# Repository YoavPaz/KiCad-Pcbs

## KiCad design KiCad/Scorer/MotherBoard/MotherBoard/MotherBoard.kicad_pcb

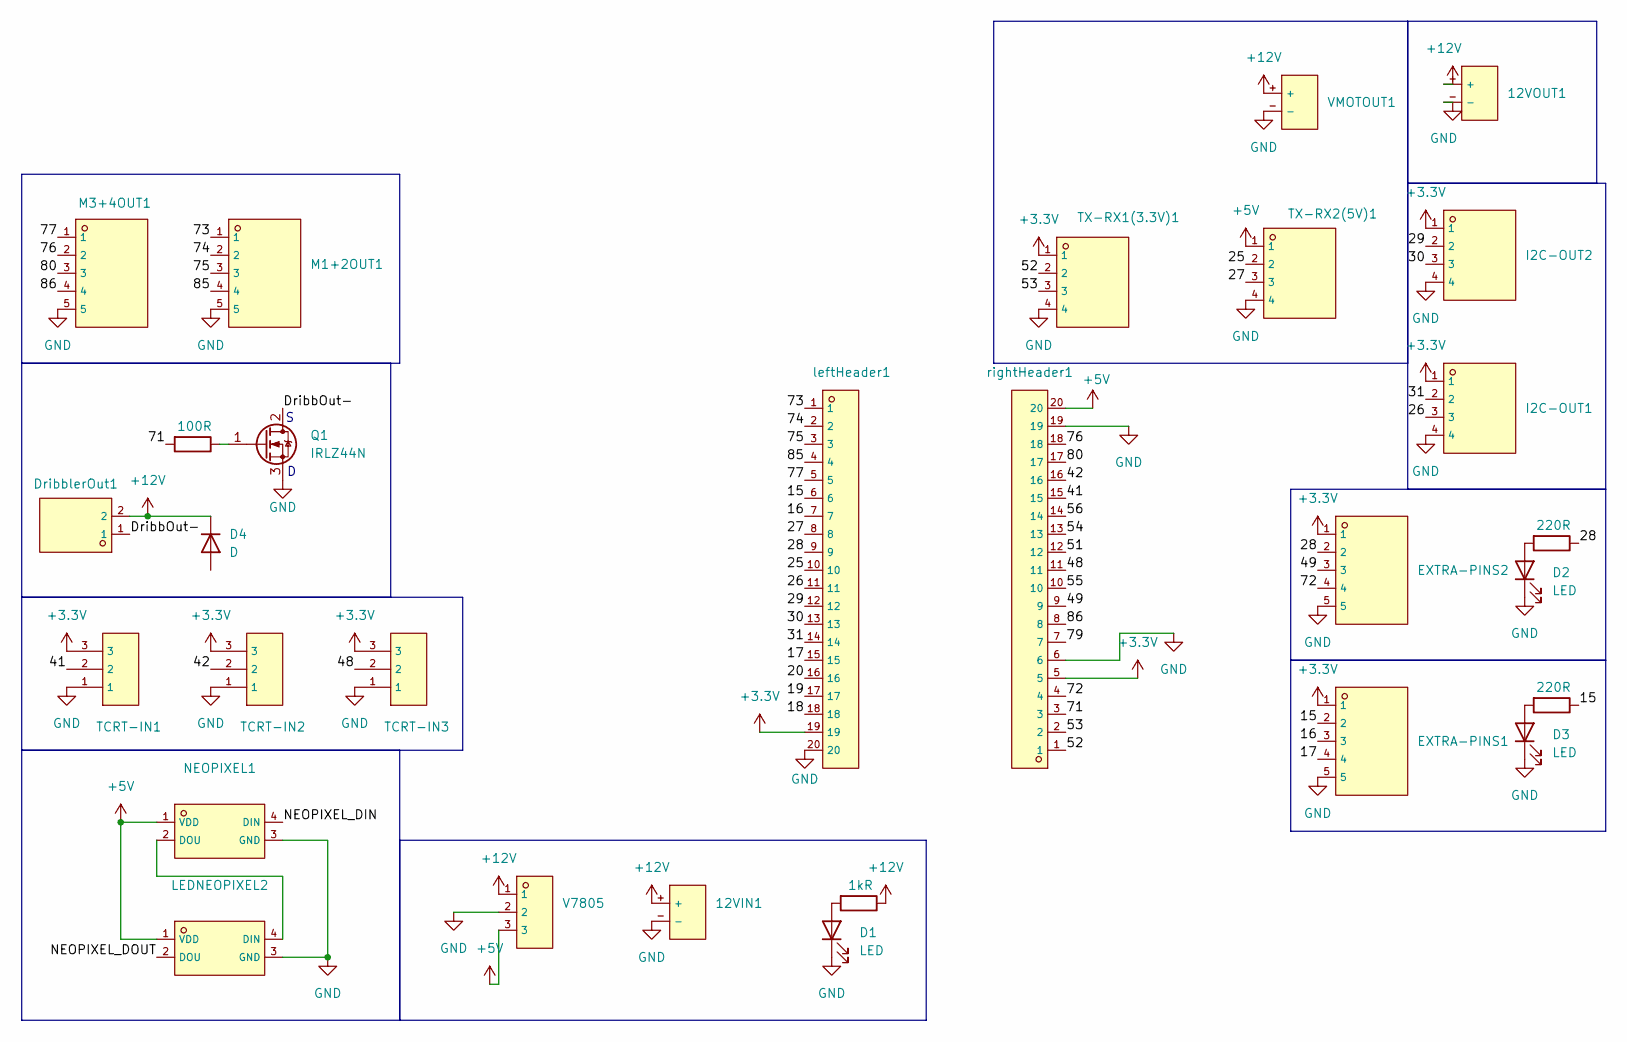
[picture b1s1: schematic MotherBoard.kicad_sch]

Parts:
12VIN1, 12VOUT1: XT60PB-F.G.Y; C19268038_CONN-TH_XT60PB-F_G_Y; LCSC C19268038
12VOKR1: 1kR; R_1206_3216Metric
15PLEDR1, 28PLEDR1: 220R; R_1206_3216Metric
D1, D2, D3: LED; LED_1206_3216Metric
D4: D; D_1206_3216Metric
DribblerOut1: B2B-XH-A (LF)(SN); C158012_CONN-TH_B2B-XH-A-LF-SN; LCSC C158012
EXTRA-PINS1, EXTRA-PINS2: B5B-XH-A (LF)(SN); C157991_CONN-TH_B5B-XH-A-LF-SN; LCSC C157991
GateResistor1: 100R; R_1206_3216Metric
I2C-OUT1, I2C-OUT2: B4B-XH-A(LF)(SN); C144395_CONN-TH_B4B-XH-A-LF-SN; LCSC C144395
LEDNEOPIXEL2: XL-5050RGBC-WS2812B; C2843785_LED-SMD_4P-L5_0-W5_0-BL_XL-5050RGBC; LCSC C2843785
M1+2OUT1, M3+4OUT1: B5B-XH-A (LF)(SN); C157991_CONN-TH_B5B-XH-A-LF-SN; LCSC C157991
NEOPIXEL1: XL-5050RGBC-WS2812B; C2843785_LED-SMD_4P-L5_0-W5_0-BL_XL-5050RGBC; LCSC C2843785
Q1: IRLZ44N; TO-220-3_Vertical
TCRT-IN1, TCRT-IN2, TCRT-IN3: B3B-XH-A(LF)(SN); C144394_CONN-TH_3P-P2_50_A2501WV2-3P; LCSC C144394
TX-RX1(3.3V)1, TX-RX2(5V)1: B4B-XH-A(LF)(SN); C144395_CONN-TH_B4B-XH-A-LF-SN; LCSC C144395
V7805: DS1023-1X3SF11; C7509516_HDR-TH_3P-P2_54-V-F-1; LCSC C7509516
VMOTOUT1: XT60PB-F.G.Y; C19268038_CONN-TH_XT60PB-F_G_Y; LCSC C19268038
leftHeader1: ZX-PM2.54-1-20PY; C7499336_HDR-TH_20P-P2_54-V-F; LCSC C7499336
rightHeader1: ZX-PM2.54-1-20PY; C7499336_HDR-TH_20P-P2_54-V-F; LCSC C7499336

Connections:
+3.3V: EXTRA-PINS1.1, EXTRA-PINS2.1, I2C-OUT1.1, I2C-OUT2.1, TCRT-IN1.3, TCRT-IN2.3, TCRT-IN3.3, TX-RX1(3.3V)1.1, leftHeader1.19, rightHeader1.5
+5V: LEDNEOPIXEL2.1 (VDD), NEOPIXEL1.1 (VDD), TX-RX2(5V)1.1, V7805.3, rightHeader1.20
+12V: 12VIN1.+, 12VOKR1.1, 12VOUT1.+, D4.1 (K), DribblerOut1.2, V7805.1, VMOTOUT1.+
/15: 15PLEDR1.1, EXTRA-PINS1.2, leftHeader1.6
/16: EXTRA-PINS1.3, leftHeader1.7
/17: EXTRA-PINS1.4, leftHeader1.15
/18: leftHeader1.18
/19: leftHeader1.17
/20: leftHeader1.16
/25: TX-RX2(5V)1.2, leftHeader1.10
/26: I2C-OUT1.3, leftHeader1.11
/27: TX-RX2(5V)1.3, leftHeader1.8
/28: 28PLEDR1.1, EXTRA-PINS2.2, leftHeader1.9
/29: I2C-OUT2.2, leftHeader1.12
/30: I2C-OUT2.3, leftHeader1.13
/31: I2C-OUT1.2, leftHeader1.14
/41: TCRT-IN1.2, rightHeader1.15
/42: TCRT-IN2.2, rightHeader1.16
/48: TCRT-IN3.2, rightHeader1.11
/49: EXTRA-PINS2.3, rightHeader1.9
/51: rightHeader1.12
/52: TX-RX1(3.3V)1.2, rightHeader1.1
/53: TX-RX1(3.3V)1.3, rightHeader1.2
/54: rightHeader1.13
/55: rightHeader1.10
/56: rightHeader1.14
/71: GateResistor1.2, rightHeader1.3
/72: EXTRA-PINS2.4, rightHeader1.4
/73: M1+2OUT1.1, leftHeader1.1
/74: M1+2OUT1.2, leftHeader1.2
/75: M1+2OUT1.3, leftHeader1.3
/76: M3+4OUT1.2, rightHeader1.18
/77: M3+4OUT1.1, leftHeader1.5
/79: rightHeader1.7
/80: M3+4OUT1.3, rightHeader1.17
/85: M1+2OUT1.4, leftHeader1.4
/86: M3+4OUT1.4, rightHeader1.8
/DribbOut-: DribblerOut1.1, Q1.2 (D)
/NEOPIXEL_DIN: NEOPIXEL1.4 (DIN)
/NEOPIXEL_DOUT: LEDNEOPIXEL2.2 (DOU)
GND: 12VIN1.-, 12VOUT1.-, D1.1 (K), D2.1 (K), D3.1 (K), EXTRA-PINS1.5, EXTRA-PINS2.5, I2C-OUT1.4, I2C-OUT2.4, LEDNEOPIXEL2.3 (GND), M1+2OUT1.5, M3+4OUT1.5, NEOPIXEL1.3 (GND), Q1.3 (S), TCRT-IN1.1, TCRT-IN2.1, TCRT-IN3.1, TX-RX1(3.3V)1.4, TX-RX2(5V)1.4, V7805.2, VMOTOUT1.-, leftHeader1.20, rightHeader1.6, rightHeader1.19
unnamed: 12VOKR1.2, D1.2 (A)
unnamed: 28PLEDR1.2, D2.2 (A)
unnamed: 15PLEDR1.2, D3.2 (A)
unnamed: LEDNEOPIXEL2.4 (DIN), NEOPIXEL1.2 (DOU)
unnamed: GateResistor1.1, Q1.1 (G)

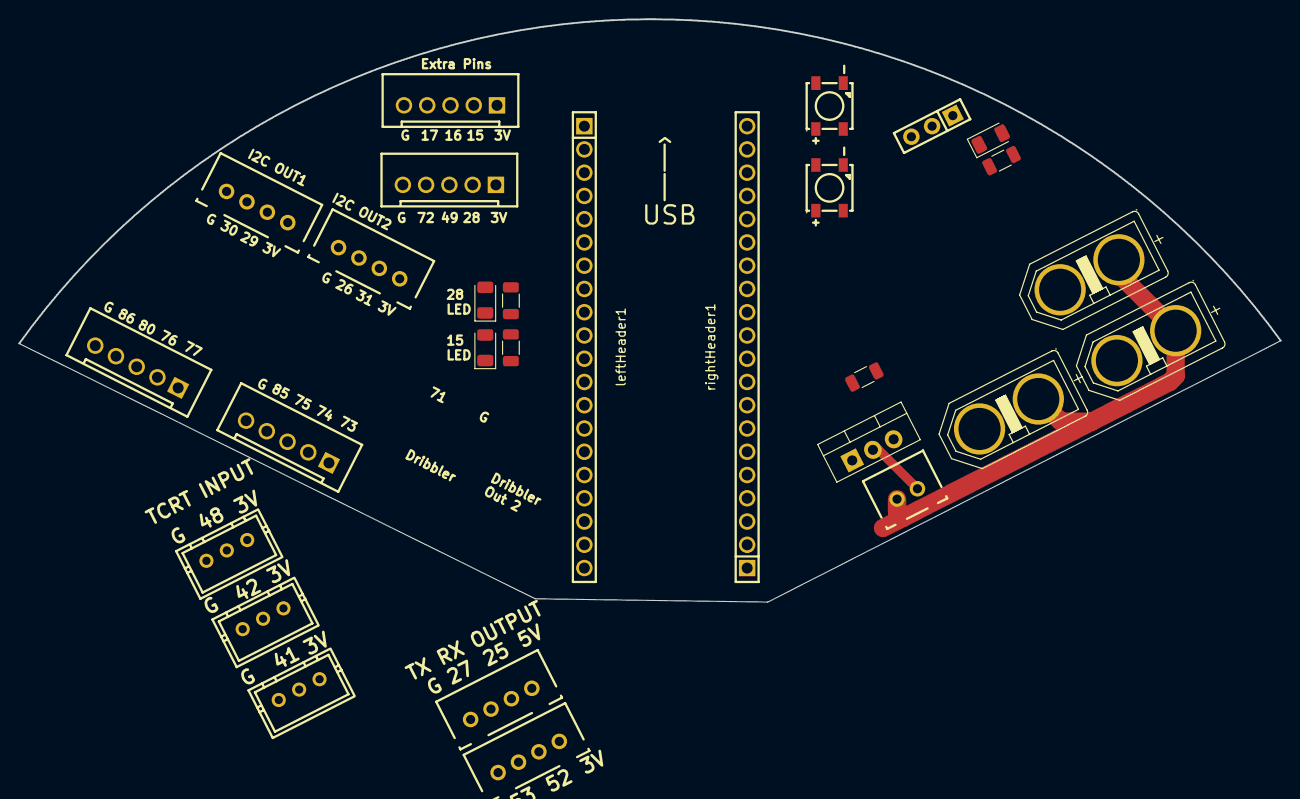
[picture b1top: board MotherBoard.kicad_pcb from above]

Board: 4 copper layers, 137.8 x 63.7 mm, 28 parts (0 on the bottom side), 36 nets.

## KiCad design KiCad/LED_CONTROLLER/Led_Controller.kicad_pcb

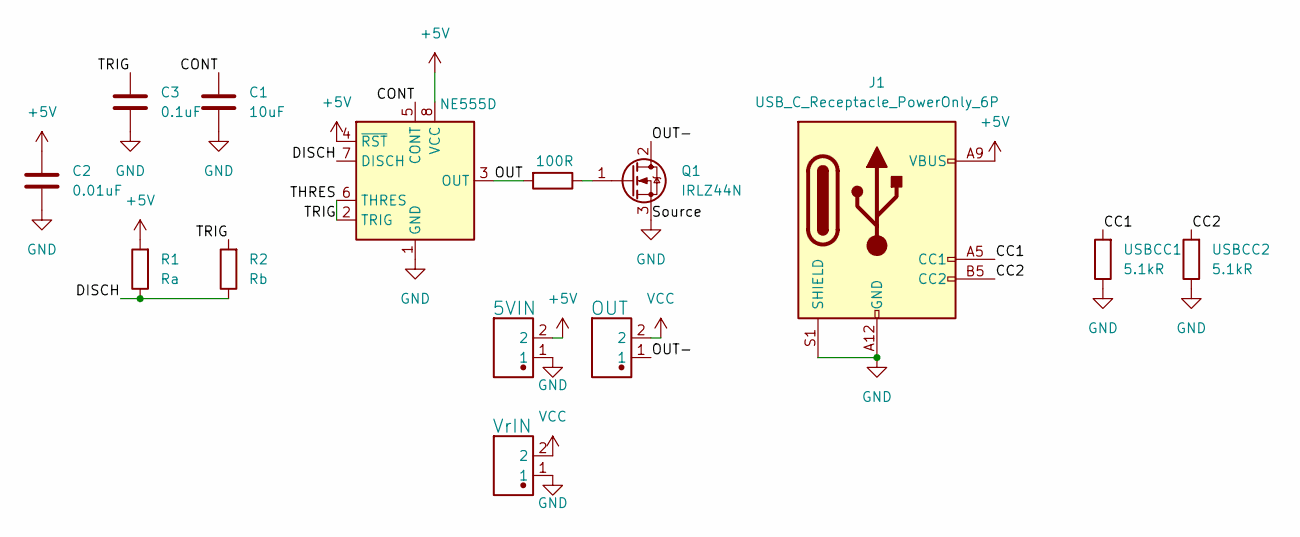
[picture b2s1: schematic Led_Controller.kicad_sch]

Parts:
5VIN1: 5VIN; JST_PH_B2B-PH-K_1x02_P2.00mm_Vertical; Manufacturer Part KH-PH-2P-Z
C1: 10uF; C_1206_3216Metric
C2: 0.01uF; C_1206_3216Metric
C3: 0.1uF; CP_Elec_4x5.4
GateResistor1: 100R; R_1206_3216Metric
J1: USB_C_Receptacle_PowerOnly_6P; USB_C_Receptacle_HRO_TYPE-C-31-M-17
OUT: OUT; JST_PH_B2B-PH-K_1x02_P2.00mm_Vertical; Manufacturer Part KH-PH-2P-Z
Q1: IRLZ44N; TO-220-3_Vertical
R1: Ra; Potentiometer_Bourns_3214W_Vertical
R2: Rb; Potentiometer_Bourns_3214W_Vertical
U1: NE555D; SOIC-8_3.9x4.9mm_P1.27mm
USBCC1, USBCC2: 5.1kR; R_1206_3216Metric
VrIN1: VrIN; JST_PH_B2B-PH-K_1x02_P2.00mm_Vertical; Manufacturer Part KH-PH-2P-Z

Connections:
+5V: 5VIN1.2, C2.1, J1.A9 (VBUS), J1.B9 (VBUS), R1.2, U1.4 (~RST), U1.8 (VCC)
/CC1: J1.A5 (CC1), USBCC1.2
/CC2: J1.B5 (CC2), USBCC2.2
/CONT: C1.1, U1.5 (CONT)
/DISCH: R1.1, R2.1, U1.7 (DISCH)
/OUT: GateResistor1.2, U1.3 (OUT)
/OUT-: OUT.1, Q1.2 (D)
/THRES: C3.1, R2.2, U1.2 (TRIG), U1.6 (THRES)
GND: 5VIN1.1, C1.2, C2.2, C3.2, J1.A12 (GND), J1.B12 (GND), J1.S1 (SHIELD), Q1.3 (S), U1.1 (GND), USBCC1.1, USBCC2.1, VrIN1.1
unnamed: GateResistor1.1, Q1.1 (G)
VCC: OUT.2, VrIN1.2

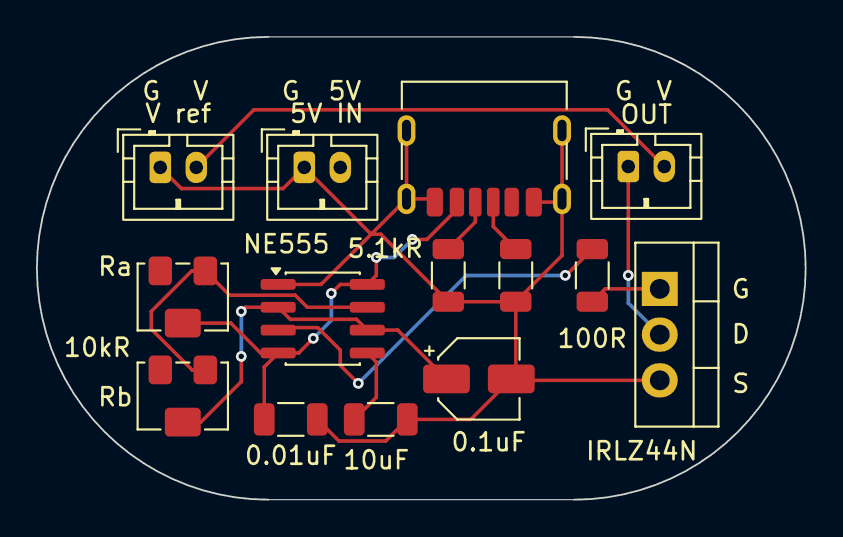
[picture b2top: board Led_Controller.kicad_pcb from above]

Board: 2 copper layers, 42.7 x 25.7 mm, 14 parts (0 on the bottom side), 11 nets.

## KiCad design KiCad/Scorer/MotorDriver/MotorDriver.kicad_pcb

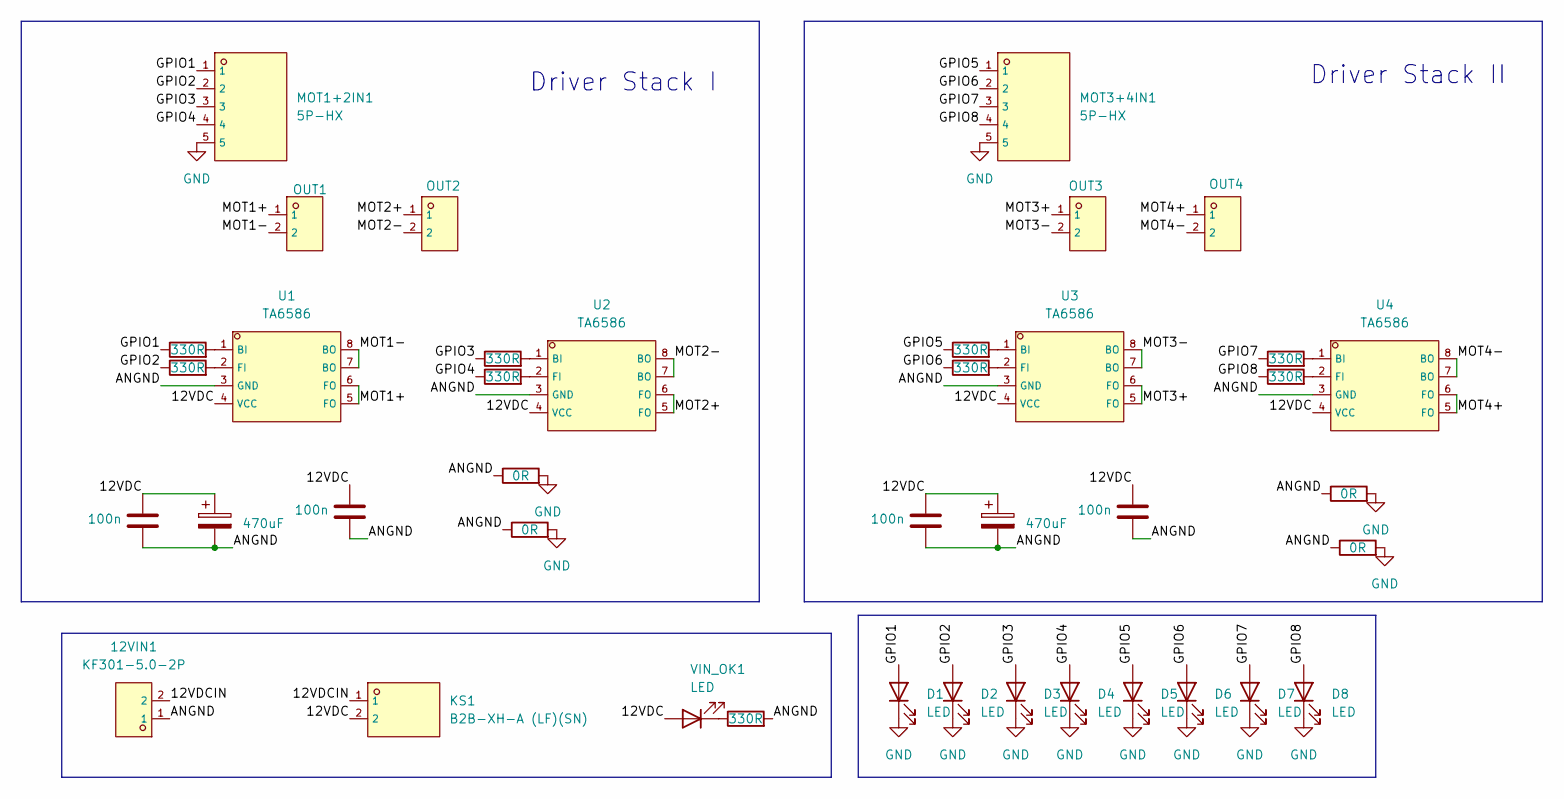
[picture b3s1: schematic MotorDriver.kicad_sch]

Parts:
12VIN1: KF301-5.0-2P; C474881_CONN-TH_P5_00_KF301-5_0-2P; LCSC C474881
C1, C3, C4, C6: 100n; C_1206_3216Metric
C2, C5: 470uF; CP_Radial_D8.0mm_P3.50mm
D1, D2, D3, D4, D5, D6, D7, D8: LED; LED_1206_3216Metric
KS1: B2B-XH-A (LF)(SN); C158012_CONN-TH_B2B-XH-A-LF-SN; LCSC C158012
MOT1+2IN1, MOT3+4IN1: 5P-HX; C157991_CONN-TH_B5B-XH-A-LF-SN; LCSC C157991
OUT1: OUT1; C474881_CONN-TH_P5_00_KF301-5_0-2P; LCSC C474881
OUT2: OUT2; C474881_CONN-TH_P5_00_KF301-5_0-2P; LCSC C474881
OUT3: OUT3; C474881_CONN-TH_P5_00_KF301-5_0-2P; LCSC C474881
OUT4: OUT4; C474881_CONN-TH_P5_00_KF301-5_0-2P; LCSC C474881
R1, R2, R5, R6, R7, R8, R9, R10, R11: 330R; R_1206_3216Metric
R3, R4, R12, R13: 0R; R_1206_3216Metric
U1, U2, U3, U4: TA6586; C128851_DIP-8_L10_0-W6_5-P2_54-LS7_6-BL; LCSC C128851
VIN_OK1: LED; LED_1206_3216Metric

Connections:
/12VDC: C1.1, C2.1, C3.1, C4.1, C5.1, C6.1, KS1.2, U1.4 (VCC), U2.4 (VCC), U3.4 (VCC), U4.4 (VCC), VIN_OK1.2 (A)
/12VDCIN: 12VIN1.2, KS1.1
/ANGND: 12VIN1.1, C1.2, C2.2, C3.2, C4.2, C5.2, C6.2, R3.1, R4.1, R11.2, R12.1, R13.1, U1.3 (GND), U2.3 (GND), U3.3 (GND), U4.3 (GND)
/GPIO1: D1.2 (A), MOT1+2IN1.1, R1.1
/GPIO2: D2.2 (A), MOT1+2IN1.2, R2.1
/GPIO3: D3.2 (A), MOT1+2IN1.3, R5.1
/GPIO4: D4.2 (A), MOT1+2IN1.4, R6.1
/GPIO5: D5.2 (A), MOT3+4IN1.1, R7.1
/GPIO6: D6.2 (A), MOT3+4IN1.2, R8.1
/GPIO7: D7.2 (A), MOT3+4IN1.3, R9.1
/GPIO8: D8.2 (A), MOT3+4IN1.4, R10.1
/MOT1+: OUT1.1, U1.5 (FO), U1.6 (FO)
/MOT1-: OUT1.2, U1.7 (BO), U1.8 (BO)
/MOT2+: OUT2.1, U2.5 (FO), U2.6 (FO)
/MOT2-: OUT2.2, U2.7 (BO), U2.8 (BO)
/MOT3+: OUT3.1, U3.5 (FO), U3.6 (FO)
/MOT3-: OUT3.2, U3.7 (BO), U3.8 (BO)
/MOT4+: OUT4.1, U4.5 (FO), U4.6 (FO)
/MOT4-: OUT4.2, U4.7 (BO), U4.8 (BO)
GND: D1.1 (K), D2.1 (K), D3.1 (K), D4.1 (K), D5.1 (K), D6.1 (K), D7.1 (K), D8.1 (K), MOT1+2IN1.5, MOT3+4IN1.5, R3.2, R4.2, R12.2, R13.2
unnamed: R1.2, U1.1 (BI)
unnamed: R2.2, U1.2 (FI)
unnamed: R5.2, U2.1 (BI)
unnamed: R6.2, U2.2 (FI)
unnamed: R7.2, U3.1 (BI)
unnamed: R8.2, U3.2 (FI)
unnamed: R9.2, U4.1 (BI)
unnamed: R10.2, U4.2 (FI)
unnamed: R11.1, VIN_OK1.1 (K)

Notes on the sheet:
Driver Stack I
Driver Stack II

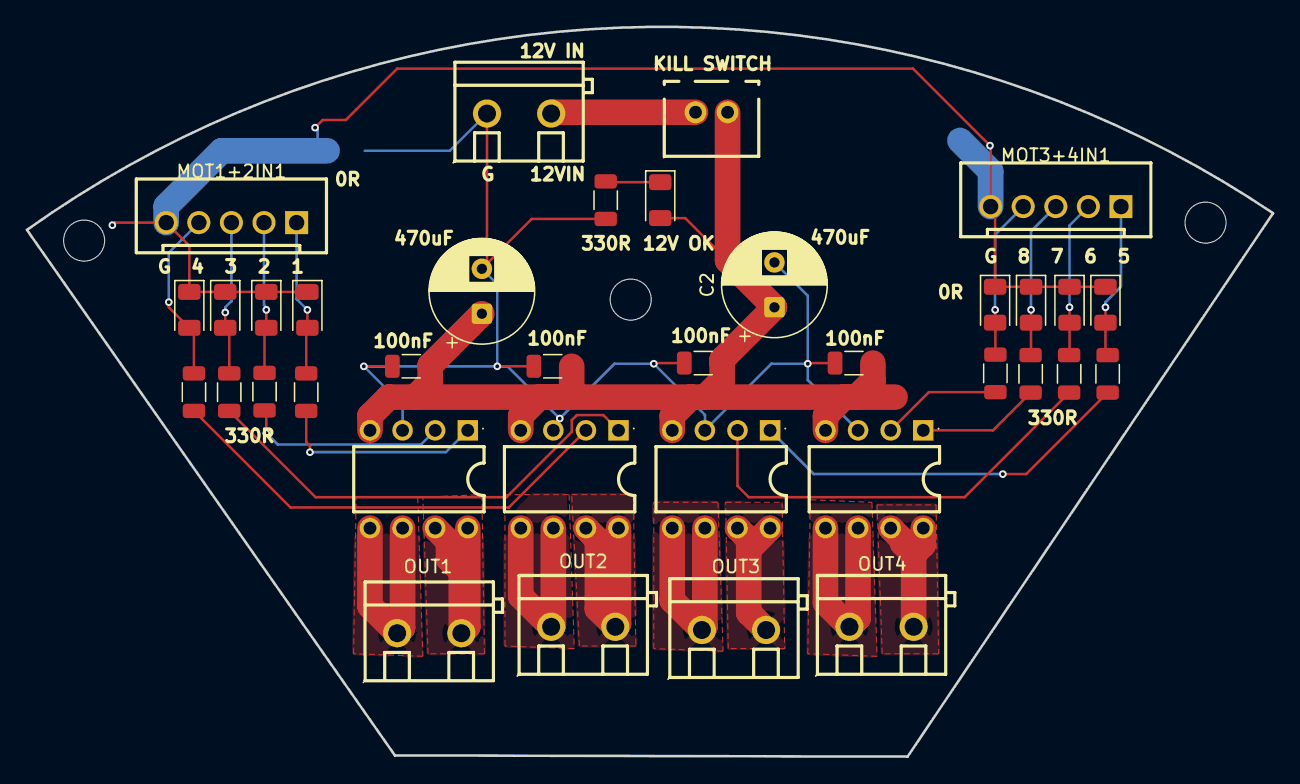
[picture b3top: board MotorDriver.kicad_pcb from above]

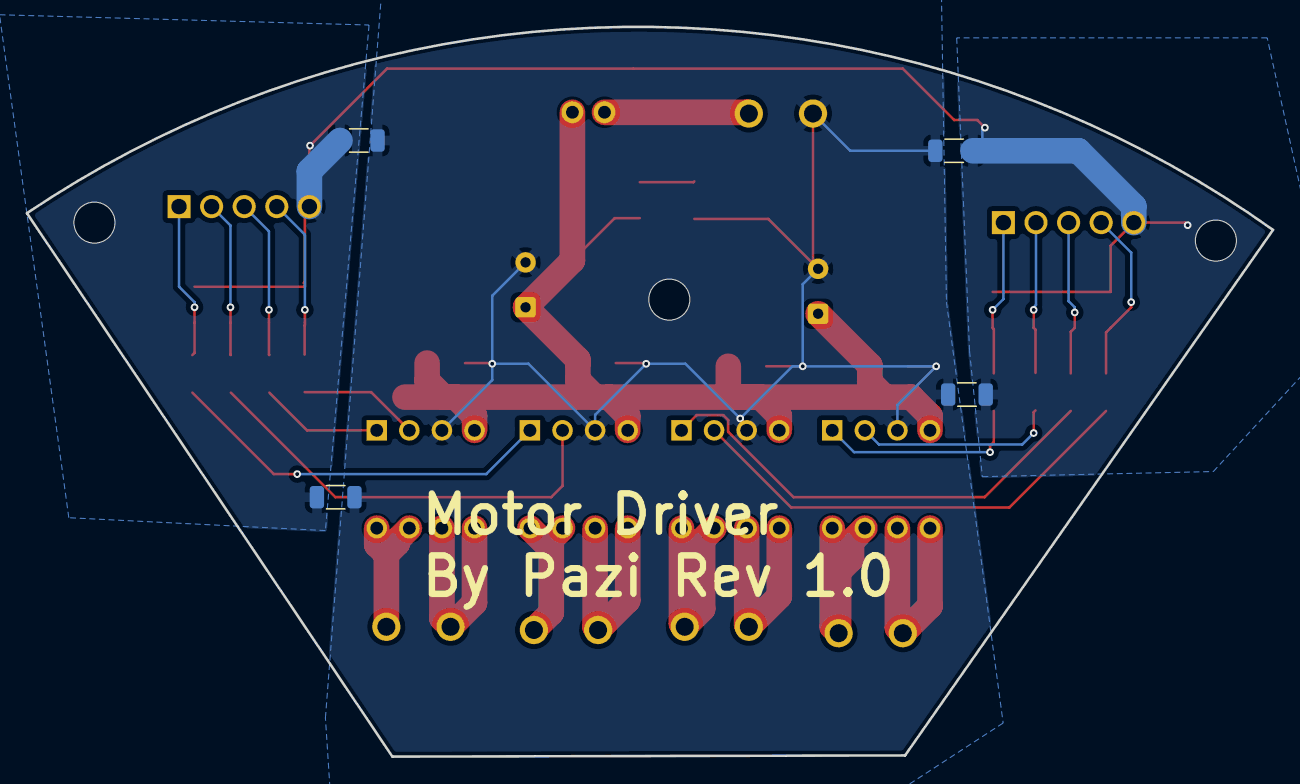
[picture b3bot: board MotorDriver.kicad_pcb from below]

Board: 2 copper layers, 97.1 x 56.9 mm, 40 parts (4 on the bottom side), 29 nets.

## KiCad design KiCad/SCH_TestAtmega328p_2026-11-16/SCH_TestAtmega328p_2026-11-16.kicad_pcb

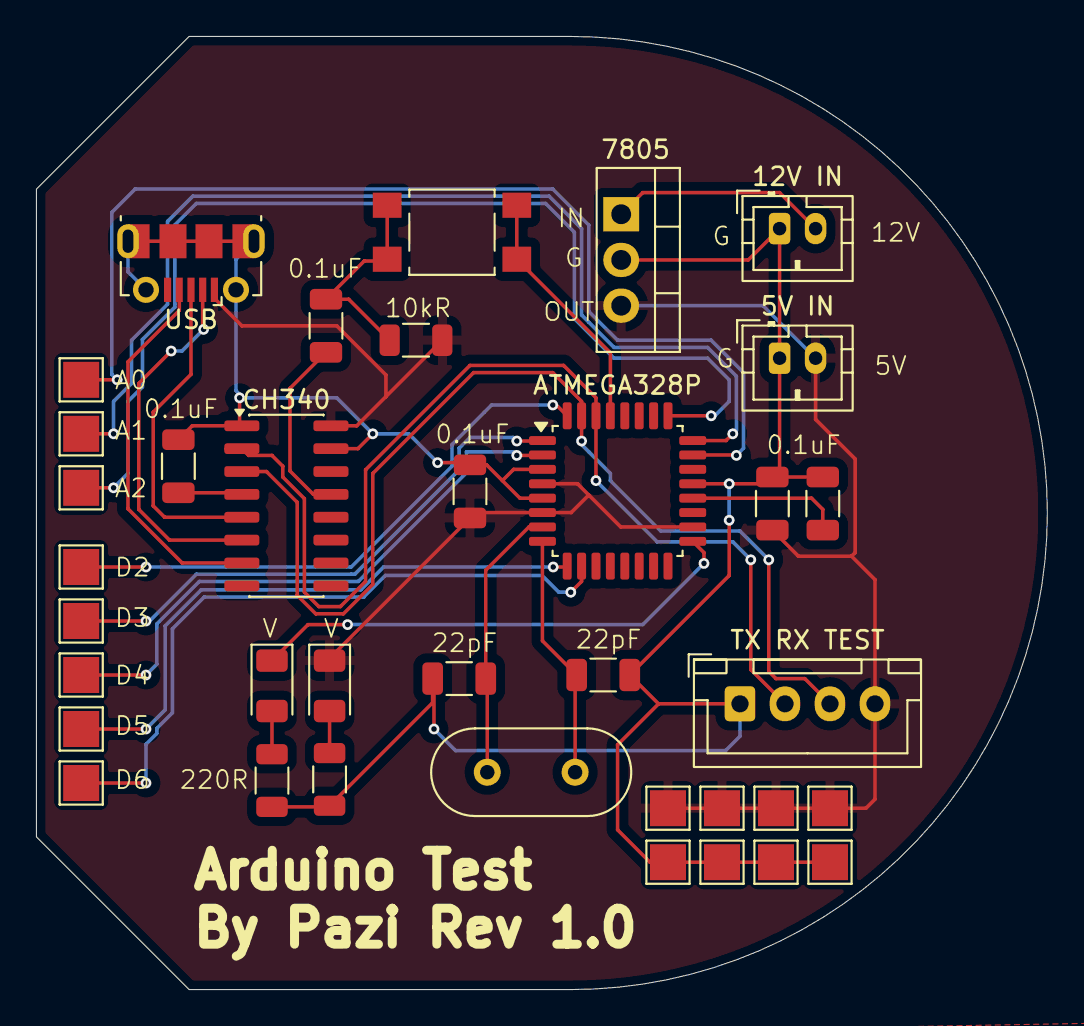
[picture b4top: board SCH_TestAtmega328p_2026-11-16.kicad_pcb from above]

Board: 2 copper layers, 56.2 x 53.0 mm, 21 parts (0 on the bottom side), 17 nets.

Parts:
5V IN: 5VIN; JST_PH_B2B-PH-K_1x02_P2.00mm_Vertical
12V IN: 12VIN; JST_PH_B2B-PH-K_1x02_P2.00mm_Vertical
22pF1, 22pF2: 22pF; C_1206_3216Metric
7805: 7805; TO-220-3_Vertical
ATMEGA328P: ATMEGA328PAU; LQFP-32_7x7mm_P0.8mm
C3, C4: 0.1uF; C_1206_3216Metric
C5, C6: 0.1u; C_1206_3216Metric
CH340: CH340C; SOIC-16_3.9x9.9mm_P1.27mm
D13_LED1: LED-0603_R; LED_1206_3216Metric
D13_R1: 220; R_1206_3216Metric
LED_R1: 220; R_1206_3216Metric
OK_LED1: LED-0603_R; LED_1206_3216Metric
RESET-RESISTOR1: 10K; R_1206_3216Metric
RESETSW1: SMD-Tactile-Switch-12X12X6MM; SW_SPST_TL3305A
TX RX TEST: XH-4PA; JST_XH_B4B-XH-A_1x04_P2.50mm_Vertical
USB: MICROXNJ; USB_Micro-B_Molex-105017-0001
VCC-GND-0.1UF1: 0.1u; C_1206_3216Metric
X1: 16MHz; Crystal_HC49-U_Vertical

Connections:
12VDCIN: 12V IN.2, 7805.1 (IN)
AREF: ATMEGA328P.20 (AREF), C3.2
D13: ATMEGA328P.17 (PB5(SCK/PCINT5)), D13_LED1.1
D+: CH340.5 (D+), USB.3 (D+)
D-: CH340.6 (D-), USB.2 (D-)
DTR#: C5.2, CH340.13 (DTR#)
GND: 5V IN.1, 12V IN.1, 22pF1.1, 22pF2.1, 7805.2 (GND), ATMEGA328P.3 (GND), ATMEGA328P.5 (GND), ATMEGA328P.21 (GND), C3.1, C4.2, C6.1, CH340.1 (GND), CH340.15 (R232), D13_R1.1, LED_R1.1, TX RX TEST.1, USB.5 (GND), USB.6 (SH1), VCC-GND-0.1UF1.1
NC: CH340.7 (NC.), USB.4 (ID)
unnamed: D13_LED1.2, D13_R1.2
unnamed: LED_R1.2, OK_LED1.2
RESET: ATMEGA328P.29 (PC6(RESET#/PCINT14)), C5.1, RESET-RESISTOR1.1, RESETSW1.1 (A), RESETSW1.2 (B)
RX: ATMEGA328P.30 (PD0(RXD/PCINT16)), CH340.2 (TXD), TX RX TEST.2
TX: ATMEGA328P.31 (PD1(TXD/PCINT17)), CH340.3 (RXD), TX RX TEST.3
V3: C6.2, CH340.4 (V3)
VCC: 5V IN.2, 7805.3 (OUT), ATMEGA328P.4 (VCC), ATMEGA328P.6 (VCC), ATMEGA328P.18 (AVCC), C4.1, CH340.16 (VCC), OK_LED1.1, RESET-RESISTOR1.2, TX RX TEST.4, USB.1 (VBUS), VCC-GND-0.1UF1.2
XTAL1: 22pF1.2, ATMEGA328P.7 ((PCINT6/XTAL1/TOSC1)PB6), X1.1
XTAL2: 22pF2.2, ATMEGA328P.8 ((PCINT7/XTAL2/TOSC2)PB7), X1.2
